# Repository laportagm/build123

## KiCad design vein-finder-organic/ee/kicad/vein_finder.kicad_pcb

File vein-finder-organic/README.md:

# Vein Finder · Organic

A palm-sized, naked-eye **transillumination vein finder** shaped like a water-worn river stone.
It presses on the forearm and side-lights the skin with visible red light. Veins show as dark
lines inside an open crescent window. There is no camera, no screen and no app: the skin is
the display.

> ### ⚠ Personal prototype for bench evaluation — not a cleared medical device
> Not for diagnosis, treatment or clinical use on patients. Built and documented for
> one person's bench evaluation in a home workshop.

## Status by gate
| Gate | Deliverable | Status |
|---|---|---|
| 1 Concept | one-page concept, three forms as renders, chosen form + why | **done; reviewed 2026-10-11** (answers in `docs/01-concept/concept.md` §9) |
| 2 CAD | parametric build123d model, STEP + print-ready 3MF, wall/fit/overhang reports | **done** — `docs/02-cad/cad.md`; updated at gate 3 for the real parts (errata: three unreported thin floors, now fixed) |
| 3 Electronics | schematic, PCB (KiCad 7), BOM with links and prices | **done** — `docs/03-electronics/electronics.md`; routed board, DRC 0 errors / 0 unconnected; the three open decisions were settled on 2026-10-12 (§7) |
| 4 Firmware | ATtiny1614 C: 3 levels, bank switch, 3-min auto-off, 41 °C limit | **done** — `docs/04-firmware/firmware.md`, `fw/` (host tests pass) |
| 5 Build + verification | print settings, illustrated assembly guide; walls & fits, runtime, thermal, IEC 62471, cost | **done** — `docs/05-build/build.md`, `docs/06-verification/verification.md`; bench checks listed for the first build |
| Readiness (2026-10-12) | fixes, evidence and GO / NO-GO | **GO** to order and build for bench evaluation; **NO-GO** for skin until the bench safety checks pass; the USB-C lip (0.91 mm; 0.87 mm at the landing face) is accepted provisionally, pending bench item 20 — `docs/06-verification/readiness.md` |
| Prototype checklist | order, build and test the first prototype, step by step | **ready** — `docs/08-prototype/checklist.md` |
| Build packet (2026-10-12) | status, order list, print packet, build-day checklist, bench data sheet, return loop for the first unit | **ready; nothing built yet** — `docs/08-prototype/README.md`; log in `docs/BUILD-LOG.md` |

## Layout
```
cad/stone/organic.py        G2 "inflated planform" surface engine (single periodic C2 B-spline skin, G2 poles)
cad/stone/verify_g2.py      ring / seam / equator curvature-continuity tests
cad/concepts/               gate 1: the three concept forms, feasibility, review renders
cad/device/params.py        gate 2: every internal dimension (single source of truth)
cad/device/skin.py          device skin (form A + thumb dish) and inner offset ("cavity") solids
cad/device/layout.py        PCB outline, LED ring, magnets, seam mask, bridge, USB-C from the real cavity
cad/device/parts.py         top shell, sole, seam mask, button bridge + stand-ins for bought parts
cad/device/checks.py        walls, overhang, interference, mass, button force (shell Ritz), magnet pull
cad/device/build.py         build -> BREP cache, STEP, PLY, 3MF, checks
calc/                       physics notes, concept budgets, pinning tests
render/                     Mitsuba 3 studio, concept and CAD renders
docs/01-concept/            concept.pdf (A3 board), concept.md (evidence), renders, figures, STEP
docs/02-cad/                cad.md (gate-2 report), renders, figures, step.zip, 3mf/, pcb/ (DXF + layout.json)
ee/design.py                gate 3: every part, net, footprint and source (single source of truth)
ee/make_schematic.py        KiCad 7 schematic + netlist round-trip check + PDF
ee/placement.py, room.py    placement proved against the shell's headroom and keep-outs
ee/make_pcb.py              board from the CAD outline, Freerouting, pours, DRC, Gerbers
ee/finish_route.py          routing finisher: edge-rule rip-up, remaining joins, GND stitching
ee/silk.py                  silkscreen tidy-up (references, labels)
ee/make_order.py            order pack (docs/07-order) from the BOM
ee/make_bom.py              BOM (CSV + Markdown) with order quantities and cost
ee/check_fab.py             read-only cross-check: DRC, nets, BOM, order pack, Gerbers, edge, outline
ee/check_fit.py             read-only: the board as built against the CAD layout (pockets, USB-C, headroom)
ee/kicad/                   KiCad project (schematic, PCB, project rules)
ee/lib/                     project symbols and footprints (libgen.py)
fw/                         gate 4: ATtiny1614 firmware (src/), host tests (test/), Makefile
docs/03-electronics/        electronics.md, bom, budget.py, optics.py, figures, fab/ (Gerbers, drill, pos)
docs/04-firmware/           firmware.md
docs/05-build/              build.md: print settings and the illustrated assembly guide
docs/06-verification/       verification.md, thermal.py, iec62471.py
docs/07-order/              order.md: PCB settings and cart files for Digi-Key, LCSC, Adafruit
docs/08-prototype/          checklist.md (procedures); the first unit's build packet (README.md): status,
                            order list, print packet, build-day list, bench data sheet, return loop
docs/BUILD-LOG.md           dated log of the physical build and its revisions (continues the N-register)
tools/fetch.sh              fetches KiCad 7 library files, Freerouting and avr-gcc into build/
build/                      generated (gitignored)
```

## Rebuild
```bash
pip install -r requirements.txt
# gate 1
cd cad/concepts && python build_concept.py A && python feasibility.py
cd ../../calc && python -m pytest -q && python concept_budget.py
cd ../render && python concept_renders.py
cd ../docs/01-concept && python figures.py && python build_pdf.py
# gate 2
cd ../../cad/device && python layout.py && python build.py --force --3mf --checks && python verify_skin.py
cd ../../render && python cad_renders.py --spp 128 --scale 1.0
cd ../docs/02-cad && python figures.py && python package.py
# gates 3-5 (KiCad 7 + Java for Freerouting; tools/fetch.sh gets the rest)
cd ../.. && tools/fetch.sh
python ee/libgen.py && python ee/make_schematic.py && python ee/make_bom.py && python ee/make_order.py
python ee/make_pcb.py --no-fab && python ee/finish_route.py && python ee/make_pcb.py --stage finish
python ee/plot_pcb.py && (cd docs/03-electronics && python budget.py && python optics.py)
python ee/check_fab.py      # read-only: the committed board, BOM, order pack and fab files agree
python ee/check_fit.py      # read-only: the board as built meets the enclosure's layout
make -C fw test && make -C fw && make -C fw mutants
(cd docs/06-verification && python thermal.py && python iec62471.py)
python docs/08-prototype/print_dims.py && python docs/08-prototype/make_bench_sheet.py   # build packet
```

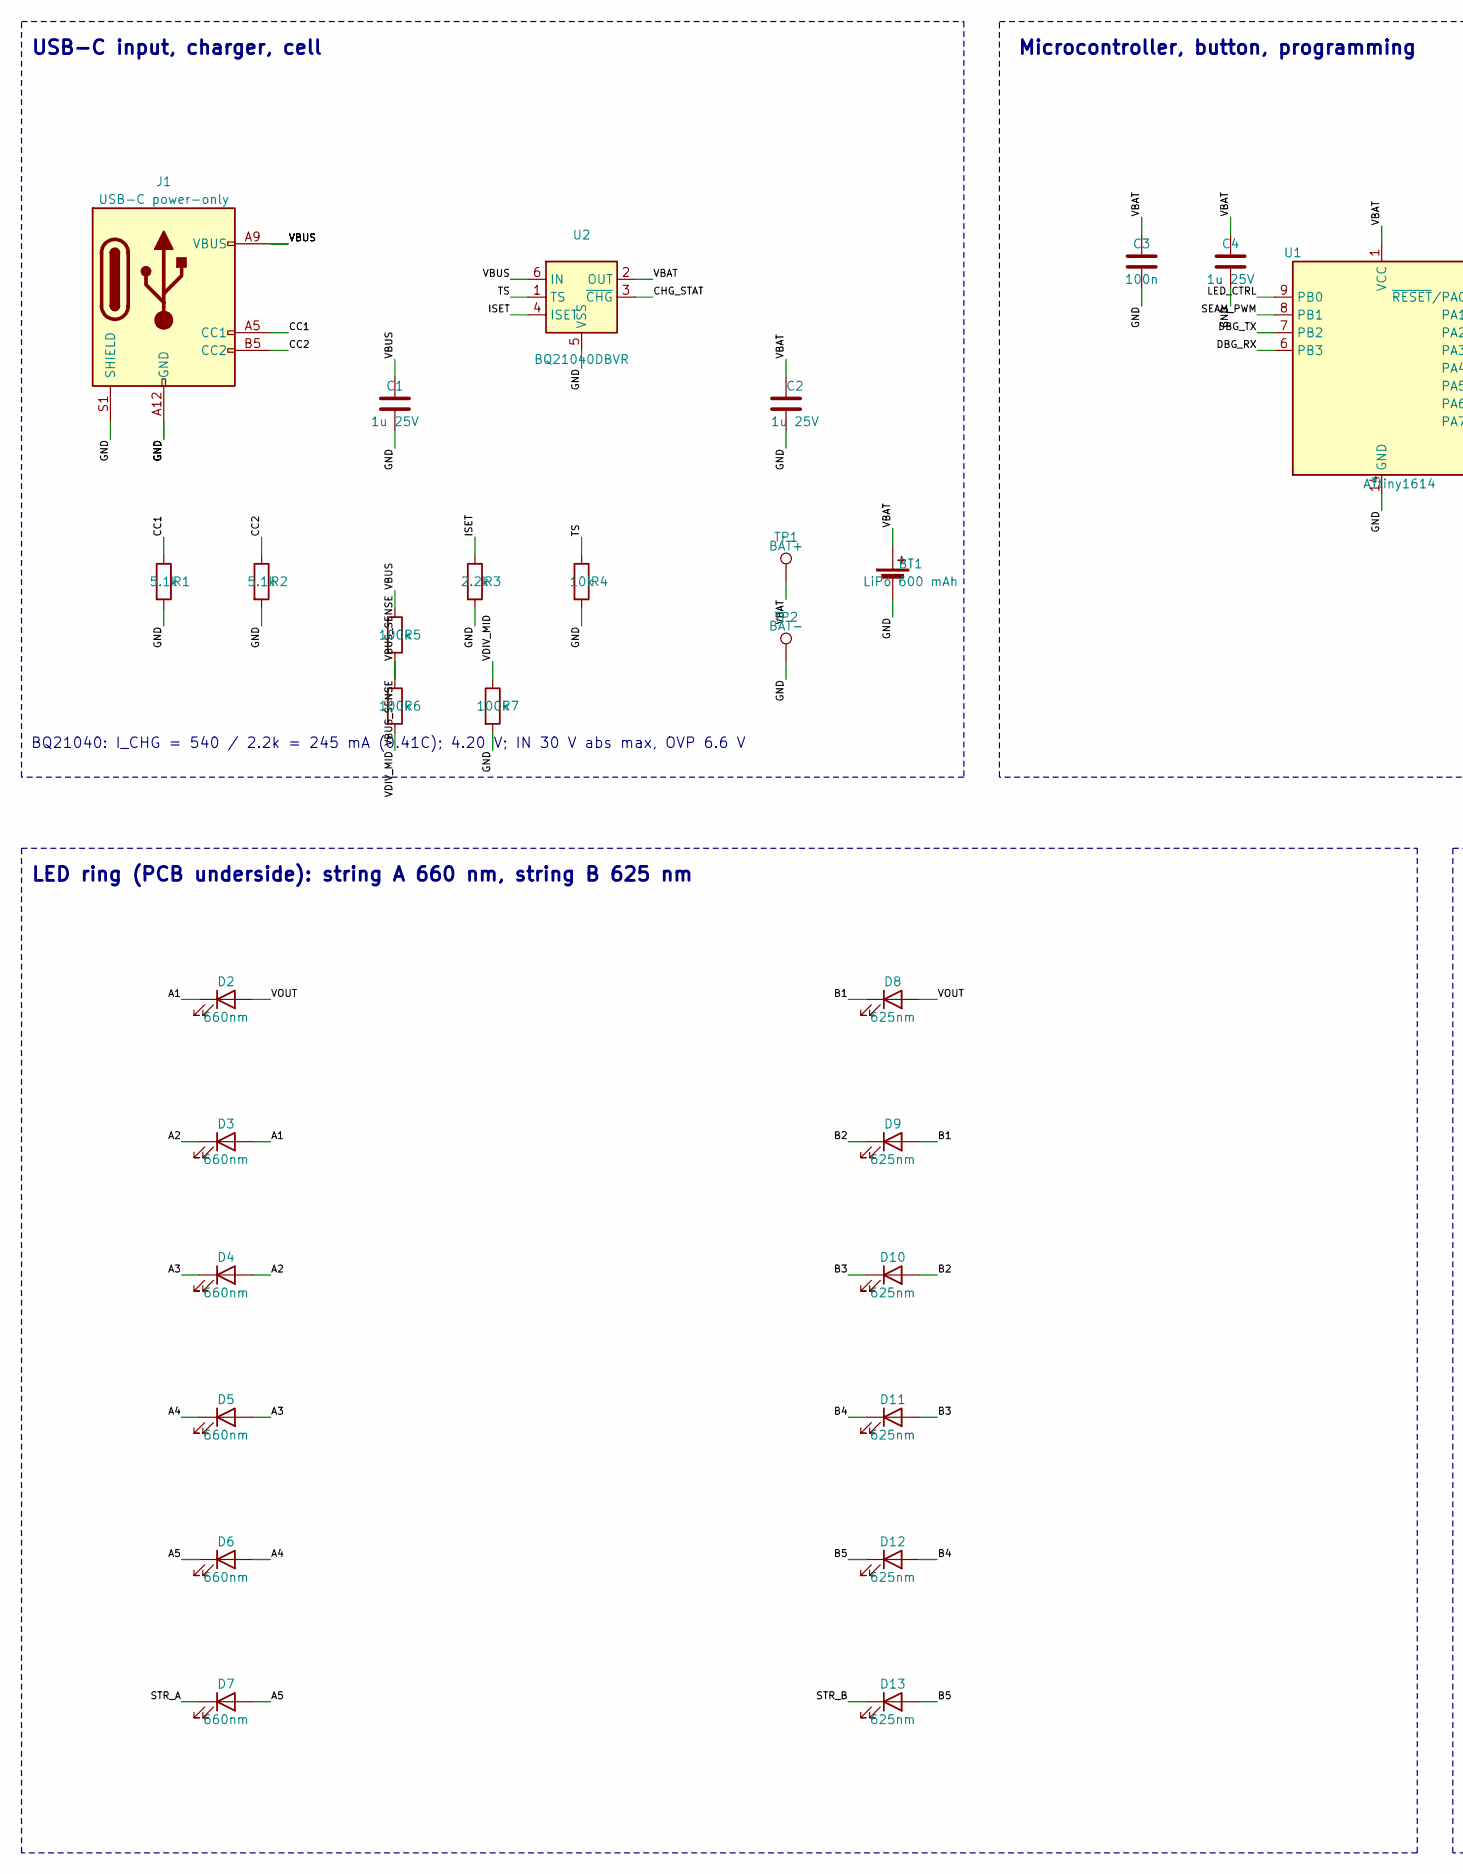
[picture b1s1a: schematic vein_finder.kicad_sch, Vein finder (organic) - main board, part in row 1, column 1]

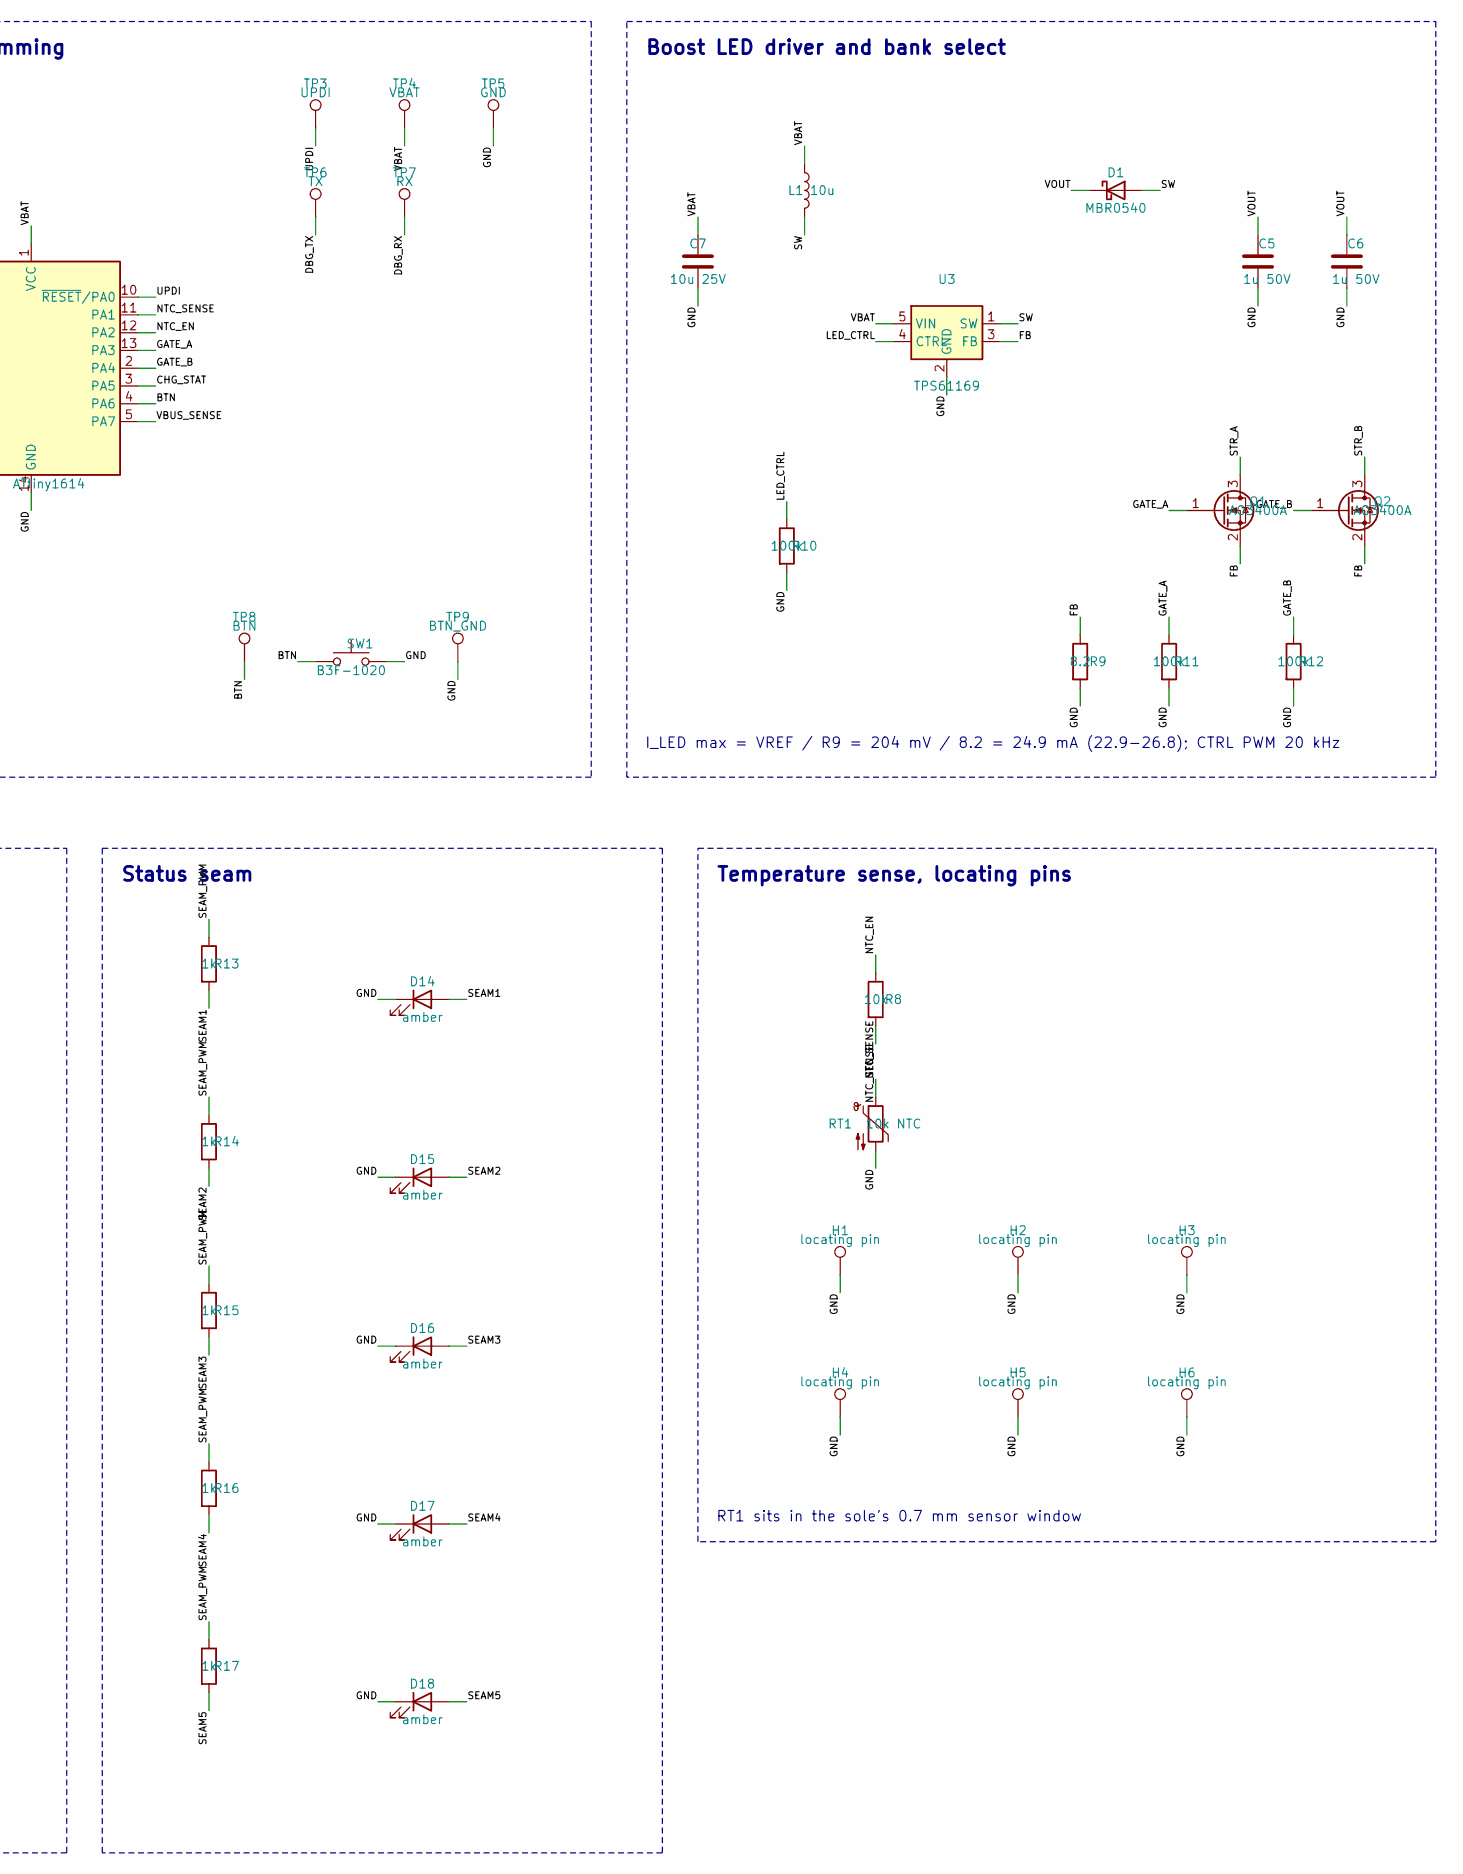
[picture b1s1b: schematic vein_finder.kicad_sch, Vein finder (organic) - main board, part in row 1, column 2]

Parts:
BT1: LiPo 600 mAh; MPN LP503040JH+PCM+2 WIRES 50MM
C1, C2, C4: 1u 25V; C_0603_1608Metric_Pad1.08x0.95mm_HandSolder; MPN CL10B105KA8NNNC
C3: 100n; C_0603_1608Metric_Pad1.08x0.95mm_HandSolder; MPN CL10B104KB8NNNC
C5, C6: 1u 50V; C_1206_3216Metric_Pad1.33x1.80mm_HandSolder; MPN CL31B105KBHNNNE
C7: 10u 25V; C_0805_2012Metric_Pad1.18x1.45mm_HandSolder; MPN GRM21BR61E106KA73L
D1: MBR0540; D_SOD-123; MPN MBR0540T1G
D2, D3, D4, D5, D6, D7: 660nm; LED_1206_3216Metric_Pad1.42x1.75mm_HandSolder; MPN XZM2MR55W-3
D8, D9, D10, D11, D12, D13: 625nm; LED_1206_3216Metric_Pad1.42x1.75mm_HandSolder; MPN XZM2CRK55W-3
D14, D15, D16, D17, D18: amber; LED_0603_1608Metric; MPN LTST-C190KSKT
H1: locating pin; LocatingPin_D1.0mm; MPN PRPC040SAAN-RC
H2, H3, H4, H5, H6: locating pin; LocatingPin_D1.0mm
J1: USB-C power-only; USB_C_GCT_USB4515-GF-A_MidMount; MPN USB4515-GF-A
L1: 10u; L_Sunlord_SWPA4018S; MPN SWPA4018S100MT
Q1, Q2: AO3400A; SOT-23; MPN AO3400A
R1, R2: 5.1k; R_0603_1608Metric_Pad0.98x0.95mm_HandSolder; MPN 0603WAF5101T5E
R3: 2.2k; R_0603_1608Metric_Pad0.98x0.95mm_HandSolder; MPN 0603WAF2201T5E
R4, R8: 10k; R_0603_1608Metric_Pad0.98x0.95mm_HandSolder; MPN RC0603FR-0710KL
R5, R6, R7, R10, R11, R12: 100k; R_0603_1608Metric_Pad0.98x0.95mm_HandSolder; MPN RC0603FR-07100KL
R9: 8.2; R_0603_1608Metric_Pad0.98x0.95mm_HandSolder; MPN RC0603FR-078R2L
R13, R14, R15, R16, R17: 1k; R_0603_1608Metric_Pad0.98x0.95mm_HandSolder; MPN RC0603FR-071KL
RT1: 10k NTC; R_0603_1608Metric_Pad0.98x0.95mm_HandSolder; MPN NCP18XH103F03RB
SW1: B3F-1020; MPN B3F-1020
TP1: BAT+; WirePad_1.5x3.0mm
TP2: BAT-; WirePad_1.5x3.0mm
TP3: UPDI; TestPoint_Pad_1.5x1.5mm
TP4: VBAT; TestPoint_Pad_1.5x1.5mm
TP5: GND; TestPoint_Pad_1.5x1.5mm
TP6: TX; TestPoint_Pad_1.5x1.5mm
TP7: RX; TestPoint_Pad_1.5x1.5mm
TP8: BTN; WirePad_1.2x2.0mm
TP9: BTN_GND; WirePad_1.2x2.0mm
U1: ATtiny1614; SOIC-14_3.9x8.7mm_P1.27mm; MPN ATTINY1614-SSNR
U2: BQ21040DBVR; SOT-23-6; MPN BQ21040DBVR
U3: TPS61169; SC-70-5_HandSolder; MPN TPS61169DCKR

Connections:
A1: D2.1 (K), D3.2 (A)
A2: D3.1 (K), D4.2 (A)
A3: D4.1 (K), D5.2 (A)
A4: D5.1 (K), D6.2 (A)
A5: D6.1 (K), D7.2 (A)
B1: D8.1 (K), D9.2 (A)
B2: D9.1 (K), D10.2 (A)
B3: D10.1 (K), D11.2 (A)
B4: D11.1 (K), D12.2 (A)
B5: D12.1 (K), D13.2 (A)
BTN: SW1.1, TP8.1, U1.4 (PA6)
CC1: J1.A5 (CC1), R1.1
CC2: J1.B5 (CC2), R2.1
CHG_STAT: U1.3 (PA5), U2.3 (~CHG)
DBG_RX: TP7.1, U1.6 (PB3)
DBG_TX: TP6.1, U1.7 (PB2)
FB: Q1.2 (S), Q2.2 (S), R9.1, U3.3 (FB)
GATE_A: Q1.1 (G), R11.1, U1.13 (PA3)
GATE_B: Q2.1 (G), R12.1, U1.2 (PA4)
GND: BT1.2 (-), C1.2, C2.2, C3.2, C4.2, C5.2, C6.2, C7.2, D14.1 (K), D15.1 (K), D16.1 (K), D17.1 (K), D18.1 (K), H1.1, H2.1, H3.1, H4.1, H5.1, H6.1, J1.A12 (GND), J1.B12 (GND), J1.S1 (SHIELD), R1.2, R2.2, R3.2, R4.2, R7.2, R9.2, R10.2, R11.2, R12.2, RT1.2, SW1.2, TP2.1, TP5.1, TP9.1, U1.14 (GND), U2.5 (VSS), U3.2 (GND)
ISET: R3.1, U2.4 (ISET)
LED_CTRL: R10.1, U1.9 (PB0), U3.4 (CTRL)
NTC_EN: R8.1, U1.12 (PA2)
NTC_SENSE: R8.2, RT1.1, U1.11 (PA1)
SEAM1: D14.2 (A), R13.2
SEAM2: D15.2 (A), R14.2
SEAM3: D16.2 (A), R15.2
SEAM4: D17.2 (A), R16.2
SEAM5: D18.2 (A), R17.2
SEAM_PWM: R13.1, R14.1, R15.1, R16.1, R17.1, U1.8 (PB1)
STR_A: D7.1 (K), Q1.3 (D)
STR_B: D13.1 (K), Q2.3 (D)
SW: D1.2 (A), L1.2, U3.1 (SW)
TS: R4.1, U2.1 (TS)
UPDI: TP3.1, U1.10 (~RESET/PA0)
VBAT: BT1.1 (+), C2.1, C3.1, C4.1, C7.1, L1.1, TP1.1, TP4.1, U1.1 (VCC), U2.2 (OUT), U3.5 (VIN)
VBUS: C1.1, J1.A9 (VBUS), J1.B9 (VBUS), R5.1, U2.6 (IN)
VBUS_SENSE: R5.2, R6.1, U1.5 (PA7)
VDIV_MID: R6.2, R7.1
VOUT: C5.1, C6.1, D1.1 (K), D2.2 (A), D8.2 (A)

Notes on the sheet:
USB-C input, charger, cell
Microcontroller, button, programming
Boost LED driver and bank select
LED ring (PCB underside): string A 660 nm, string B 625 nm
Status seam
Temperature sense, locating pins
BQ21040: I_CHG = 540 / 2.2k = 245 mA (0.41C); 4.20 V; IN 30 V abs max, OVP 6.6 V
I_LED max = VREF / R9 = 204 mV / 8.2 = 24.9 mA (22.9-26.8); CTRL PWM 20 kHz
RT1 sits in the sole's 0.7 mm sensor window

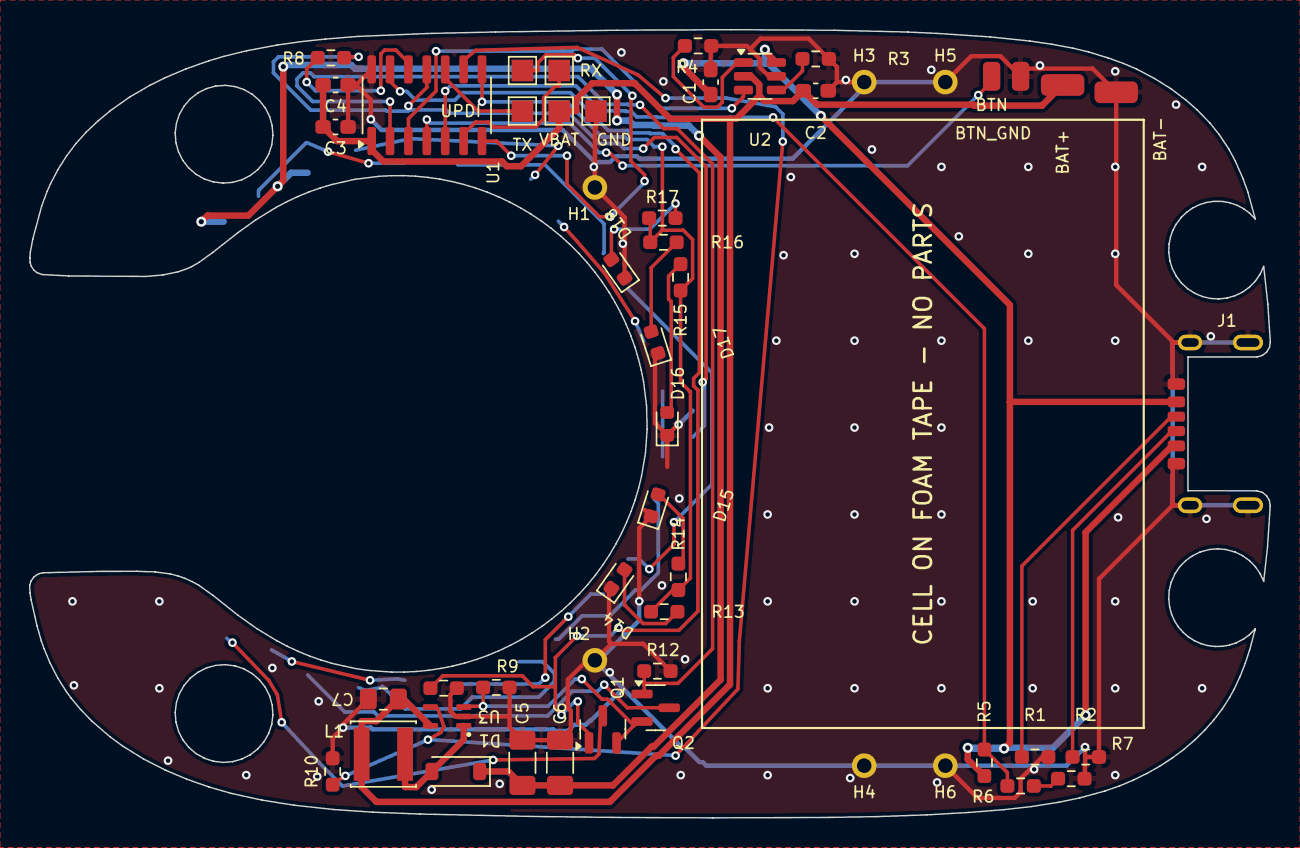
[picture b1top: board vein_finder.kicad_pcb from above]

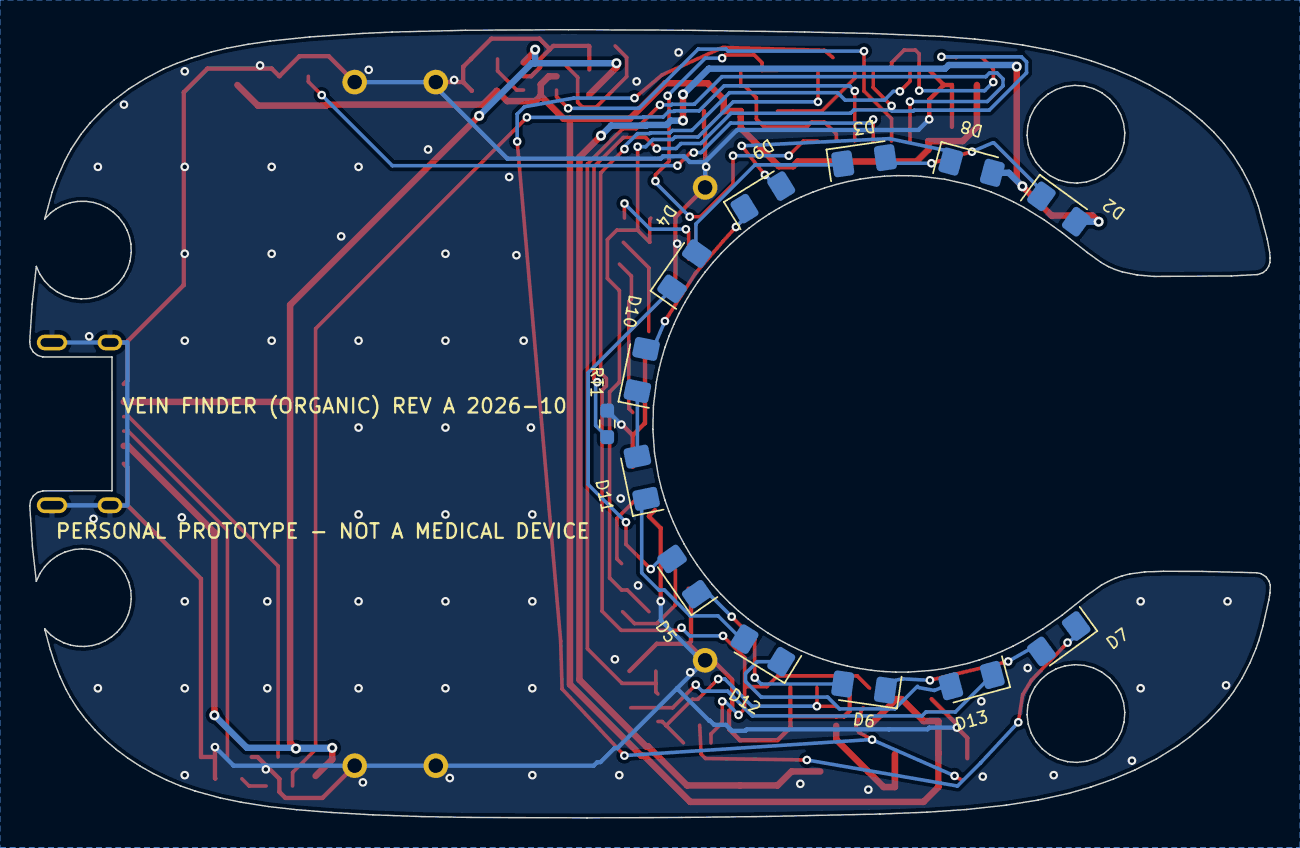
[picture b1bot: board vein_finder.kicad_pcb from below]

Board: 2 copper layers, 85.7 x 54.4 mm, 65 parts (13 on the bottom side), 40 nets.

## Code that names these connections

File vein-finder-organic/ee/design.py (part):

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
# ----------------------------------------------------------------------------- pin map
# ATtiny1614 (SOIC-14).  Chosen for: runs straight off the cell (1.8-5.5 V), UPDI needs one
# pad, TCA0 gives 2 PWM outputs on PB0/PB1, PA6 is a fully asynchronous pin (button wake).
MCU_PINS = {
    "1": "VBAT", "14": "GND",
    "10": "UPDI",        # PA0
    "11": "NTC_SENSE",   # PA1  AIN1
    "12": "NTC_EN",      # PA2  divider supply (off in sleep)
    "13": "GATE_A",      # PA3  bank A (660 nm) low-side switch
    "2": "GATE_B",       # PA4  bank B (625 nm) low-side switch
    "3": "CHG_STAT",     # PA5  charger /CHG (open drain, internal pull-up)
    "4": "BTN",          # PA6  async pin: wake from power-down
    "5": "VBUS_SENSE",   # PA7  USB present (divided to 2/3)
    "9": "LED_CTRL",     # PB0  TCA0 WO0: boost enable + PWM (analog dimming)
    "8": "SEAM_PWM",     # PB1  TCA0 WO1: status seam
    "7": "DBG_TX",       # PB2  USART0 TXD (debug pad)
    "6": "DBG_RX",       # PB3  USART0 RXD (debug pad)
}

FW_PINS = {v: k for k, v in MCU_PINS.items()}
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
